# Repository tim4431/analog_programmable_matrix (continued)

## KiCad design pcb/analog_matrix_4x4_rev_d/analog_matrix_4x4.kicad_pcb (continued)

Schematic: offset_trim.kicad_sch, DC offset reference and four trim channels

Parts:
C169, C171, C173, C174, C176, C177, C179, C180, C182, C183, C187, C189: 100n; C_0603_1608Metric; Rating 25V X7R minimum; effective C after bias
C170, C172, C188, C190: 1u; C_0805_2012Metric; Rating 25V X7R minimum; effective C after bias
C175, C178, C181, C184: 100p C0G; C_0603_1608Metric; Rating 50V C0G
C185, C186: 10u; C_0805_2012Metric; Rating 25V X7R minimum; effective C after bias
U30: AD5544BRSZ; SSOP-28_5.3x10.2mm_P0.65mm
U100, U101, U102, U103: OPA197ID; SOIC-8_3.9x4.9mm_P1.27mm
U110: ADR4525BRZ; SOIC-8_3.9x4.9mm_P1.27mm

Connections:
+5A: C169.1, C170.1, C173.1, C176.1, C179.1, C182.1, C185.1, C187.1, C188.1, U30.7 (VDD), U100.7 (V+), U101.7 (V+), U102.7 (V+), U103.7 (V+), U110.2 (VIN); also elsewhere on the board
-5A: C171.1, C172.1, C174.1, C177.1, C180.1, C183.1, C186.1, U30.23 (VSS), U100.4 (V-), U101.4 (V-), U102.4 (V-), U103.4 (V-); also elsewhere on the board
GND: C169.2, C170.2, C171.2, C172.2, C173.2, C174.2, C176.2, C177.2, C179.2, C180.2, C182.2, C183.2, C185.2, C186.2, C187.2, C188.2, C189.2, C190.2, U30.1 (AGND), U30.5 (MSB), U30.14 (AGND), U30.15 (AGND), U30.22 (AGNDF), U30.24 (DGND), U30.28 (AGND), U100.3 (+), U101.3 (+), U102.3 (+), U103.3 (+), U110.4 (GND); also elsewhere on the board
LDAC_N: U30.21 (~LDAC); also elsewhere on the board
MOSI: U30.10 (SDI); also elsewhere on the board
unnamed: C175.1, U30.2 (IOUT), U100.2 (-)
unnamed: C178.1, U30.13 (IOUT), U101.2 (-)
unnamed: C181.1, U30.16 (IOUT), U102.2 (-)
unnamed: C184.1, U30.27 (IOUT), U103.2 (-)
RESET_N: U30.6 (~RS); also elsewhere on the board
SCK: U30.9 (CLK); also elsewhere on the board
TRIM_CS: U30.8 (~CS); also elsewhere on the board
VREF_2V5: C189.1, C190.1, U30.3 (VREF), U30.12 (VREF), U30.17 (VREF), U30.26 (VREF), U110.6 (2.5V); also elsewhere on the board
VTRIM0: C175.2, U30.4 (RFB), U100.6 (OUT); also elsewhere on the board
VTRIM1: C178.2, U30.11 (RFB), U101.6 (OUT); also elsewhere on the board
VTRIM2: C181.2, U30.18 (RFB), U102.6 (OUT); also elsewhere on the board
VTRIM3: C184.2, U30.25 (RFB), U103.6 (OUT); also elsewhere on the board

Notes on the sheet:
DC offset reference and four trim channels
U30 is a fifth AD5544. VTRIM=-2.5*D/65536 V. Midscale=32768. Loaded output trim is approximately +/-131 mV.
Offset trim for b0
Offset trim for b1
Offset trim for b2
Offset trim for b3

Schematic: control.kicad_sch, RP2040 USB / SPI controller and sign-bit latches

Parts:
C191, C192: 100n; C_0603_1608Metric; Rating 25V X7R minimum; effective C after bias
R133, R134, R135, R136, R137: 33R; R_0603_1608Metric; Rating 0.1%, <=25ppm/C; 0.1W minimum
R138, R139, R140, R141, R142, R143, R144, R145, R146: 10 k; R_0603_1608Metric; Rating 0.1%, <=25ppm/C; 0.1W minimum
U120: Pico; Pico_2x20_Socket_17.78mm
U121, U122: SN74HC595D; SOIC-16_3.9x9.9mm_P1.27mm

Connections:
3V3: C191.1, C192.1, R138.2, R139.2, R140.2, R141.2, R142.2, R143.2, U120.36 (3V3_OUT), U121.10 (~SRCLR), U121.16 (VCC), U122.10 (~SRCLR), U122.16 (VCC); also elsewhere on the board
/Control/MOSI_PRE: R134.1, U120.5 (GP3)
/Control/SCK_PRE: R133.1, U120.4 (GP2)
/Control/SIGN_CHAIN: U121.9 (QH'), U122.14 (SER)
/Control/SIGN_CLK: R136.2, U121.11 (SRCLK), U122.11 (SRCLK)
/Control/SIGN_CLK_PRE: R136.1, U120.15 (GP11)
/Control/SIGN_DATA: R135.2, U121.14 (SER)
/Control/SIGN_DATA_PRE: R135.1, U120.14 (GP10)
/Control/SIGN_LATCH: R137.2, U121.12 (RCLK), U122.12 (RCLK)
/Control/SIGN_LATCH_PRE: R137.1, U120.16 (GP12)
GND: C191.2, C192.2, R144.2, R145.2, R146.2, U120.3 (GND), U120.8 (GND), U120.13 (GND), U120.18 (GND), U120.23 (GND), U120.28 (GND), U120.33 (AGND), U120.38 (GND), U121.8 (GND), U121.13 (~OE), U122.8 (GND), U122.13 (~OE); also elsewhere on the board
LDAC_N: R143.1, U120.11 (GP8); also elsewhere on the board
MOSI: R134.2; also elsewhere on the board
OUTPUT_RUN: R146.1, U120.19 (GP14); also elsewhere on the board
RESET_N: R144.1, U120.12 (GP9); also elsewhere on the board
ROW0_CS: R138.1, U120.6 (GP4); also elsewhere on the board
ROW1_CS: R139.1, U120.7 (GP5); also elsewhere on the board
ROW2_CS: R140.1, U120.9 (GP6); also elsewhere on the board
ROW3_CS: R141.1, U120.10 (GP7); also elsewhere on the board
SCK: R133.2; also elsewhere on the board
SIGN0: U121.15 (QA); also elsewhere on the board
SIGN1: U121.1 (QB); also elsewhere on the board
SIGN2: U121.2 (QC); also elsewhere on the board
SIGN3: U121.3 (QD); also elsewhere on the board
SIGN4: U121.4 (QE); also elsewhere on the board
SIGN5: U121.5 (QF); also elsewhere on the board
SIGN6: U121.6 (QG); also elsewhere on the board
SIGN7: U121.7 (QH); also elsewhere on the board
SIGN8: U122.15 (QA); also elsewhere on the board
SIGN9: U122.1 (QB); also elsewhere on the board
SIGN10: U122.2 (QC); also elsewhere on the board
SIGN11: U122.3 (QD); also elsewhere on the board
SIGN12: U122.4 (QE); also elsewhere on the board
SIGN13: U122.5 (QF); also elsewhere on the board
SIGN14: U122.6 (QG); also elsewhere on the board
SIGN15: U122.7 (QH); also elsewhere on the board
SIGNAL_EN: R145.1, U120.17 (GP13); also elsewhere on the board
TRIM_CS: R142.1, U120.20 (GP15); also elsewhere on the board

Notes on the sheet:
RP2040 USB / SPI controller and sign-bit latches
Pico is USB-powered. Do not connect VBUS/VSYS to +5A. Apply analog power first. GP14=OUTPUT_RUN and GP13=SIGNAL_EN default low.
First register QA..QH = SIGN0..7. Second register QA..QH = SIGN8..15. Clock bit 15 first, latch after 16 clocks.
SPI mode 0, 1MHz, 24 clocks: last 18 bits = channel[1:0], code[15:0]. Five separate CS nets; shared LDAC. SDO pins intentionally unused. Firmware sequence: mute -> disable sign switches -> latch signs -> load 20 DAC words -> LDAC -> settle -> restore prior armed state. No automatic rail supervisor 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

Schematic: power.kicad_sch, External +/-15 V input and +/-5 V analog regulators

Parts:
C193, C197: 47u; C_Radial_D5.0mm_H11.0mm_P2.00mm; Rating 35V polarized
C194: 330n; C_0603_1608Metric; Rating 25V X7R minimum; effective C after bias
C195, C199: 10u; C_Radial_D5.0mm_H11.0mm_P2.00mm; Rating 16V polarized
C196, C200: 100n; C_0603_1608Metric; Rating 25V X7R minimum; effective C after bias
C198: 2.2u; CP_EIA-3216-18_Kemet-A; Rating 35V polarized
D1, D2: 1N4002; D_DO-41_SOD81_P10.16mm_Horizontal
J9: 3-pin terminal; TerminalBlock_Phoenix_MKDS-1,5-3-5.08_1x03_P5.08mm_Horizont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
U130: L7805CV; TO-220-3_Vertical
U131: L7905CV; TO-220-3_Vertical

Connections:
+5A: C195.1, C196.1, D1.2 (A), U130.3 (OUT); also elsewhere on the board
+15V: C193.1, C194.1, D1.1 (K), J9.1 (+15V), U130.1 (IN); also elsewhere on the board
-5A: C199.2, C200.1, D2.1 (K), U131.3 (OUT); also elsewhere on the board
-15V: C197.2, C198.2, D2.2 (A), J9.3 (-15V), U131.2 (IN); also elsewhere on the board
GND: C193.2, C194.2, C195.2, C196.2, C197.1, C198.1, C199.1, C200.2, J9.2 (GND), U130.2 (GND), U131.1 (GND); also elsewhere on the board

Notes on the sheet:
External +/-15 V input and +/-5 V analog regulators
External regulated +/-15 V, at least 1 A per rail. Regulator heatsinks <=15 C/W. Negative regulator tab is -15 V; positive regulator tab is GND.
Observe all polarized capacitor signs. Use the shown electrolytic/tantalum regulator capacitors; do not substitute ceramic-only outputs. Regulator dissipation is roughly 3 W per device; verify temperature under sustained DC output loads. +/-5A supplies the analog core.

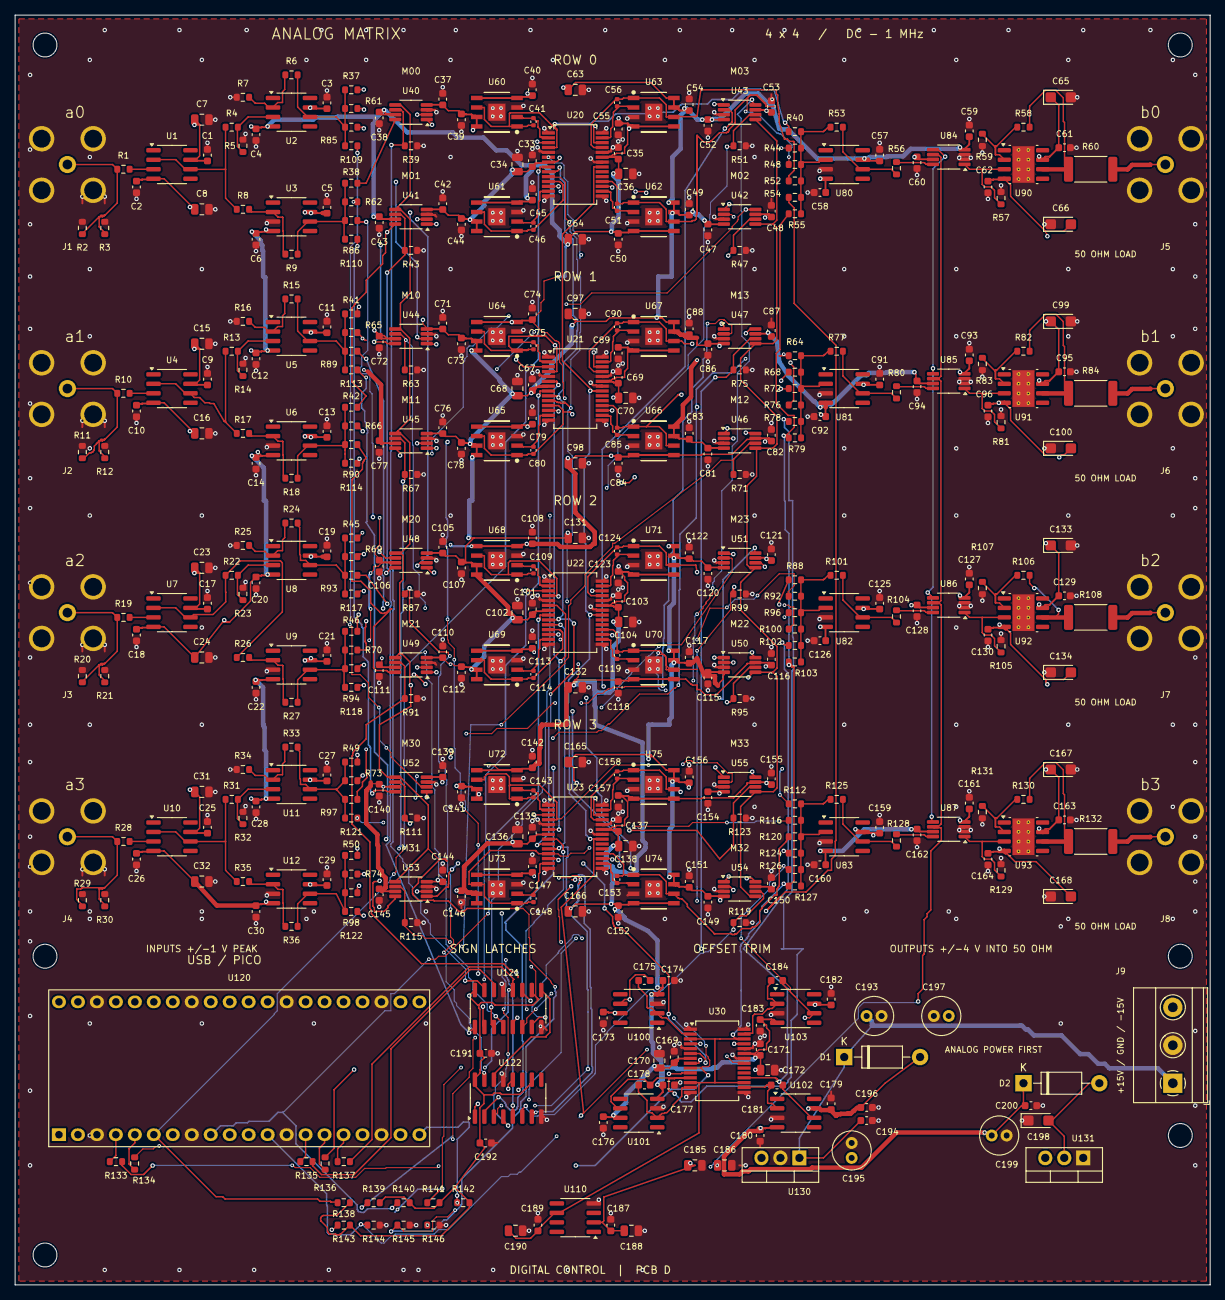
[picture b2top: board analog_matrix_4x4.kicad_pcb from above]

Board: 4 copper layers, 160.0 x 170.0 mm, 434 parts (0 on the bottom side), 191 nets.

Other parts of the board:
H1, H2, H3, H4, H5, H6: MountingHole_3.2mm_M3

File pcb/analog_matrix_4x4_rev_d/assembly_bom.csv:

References,Quantity,Value or IC MPN,Footprint,Rating,Fit
"J1, J2, J3, J4, J5, J6, J7, J8",8,BNC 031-5329-52RFX,AnalogMatrix:BNC_Amphenol_031-5329-52RFX_Vertical,,YES
"R1, R10, R19, R28, R133, R134, R135, R136, R137",9,33 ohm,AnalogMatrix:R_0603_1608Metric,"0.1%, <=25ppm/C; 0.1W minimum",YES
"R2, R11, R20, R29",4,1 M,AnalogMatrix:R_0603_1608Metric,"0.1%, <=25ppm/C; 0.1W minimum",YES
"R3, R12, R21, R30",4,49.9 ohm,AnalogMatrix:R_0603_1608Metric,"0.1%, <=25ppm/C; 0.1W minimum",DNP
"U1, U2, U3, U4, U5, U6, U7, U8, U9, U10, U11, U12, U80, U81, U82, U83",16,OPA810ID,AnalogMatrix:SOIC-8_3.9x4.9mm_P1.27mm,,YES
"C1, C2, C3, C4, C5, C6, C9, C10, C11, C12, C13, C14, C17, C18, C19, C20, C21, C22, C25, C26, C27, C28, C29, C30, C33, C35, C37, C38, C39, C40, C42, C43, C44, C45, C47, C48, C49, C50, C52, C53, C54, C55, C57, C58, C59, C60, C61, C62, C67, C69, C71, C72, C73, C74, C76, C77, C78, C79, C81, C82, C83, C84, C86, C87, C88, C89, C91, C92, C93, C94, C95, C96, C101, C103, C105, C106, C107, C108, C110, C111, C112, C113, C115, C116, C117, C118, C120, C121, C122, C123, C125, C126, C127, C128, C129, C130, C135, C137, C139, C140, C141, C142, C144, C145, C146, C147, C149, C150, C151, C152, C154, C155, C156, C157, C159, C160, C161, C162, C163, C164, C169, C171, C173, C174, C176, C177, C179, C180, C182, C183, C187, C189, C191, C192, C196, C200",136,100 nF,AnalogMatrix:C_0603_1608Metric,25V X7R minimum; effective C after bias,YES
"R4, R5, R13, R14, R22, R23, R31, R32",8,499 ohm,AnalogMatrix:R_0603_1608Metric,"0.1%, <=25ppm/C; 0.1W minimum",YES
"R6, R7, R8, R9, R15, R16, R17, R18, R24, R25, R26, R27, R33, R34, R35, R36, R40, R44, R48, R52, R64, R68, R72, R76, R88, R92, R96, R100, R112, R116, R120, R124",32,1.00 k,AnalogMatrix:R_0603_1608Metric,"0.1%, <=25ppm/C; 0.1W minimum",YES
"C7, C8, C15, C16, C23, C24, C31, C32, C63, C64, C97, C98, C131, C132, C165, C166, C185, C186",18,10 uF,AnalogMatrix:C_0805_2012Metric,25V X7R minimum; effective C after bias,YES
"U20, U21, U22, U23, U30",5,AD5544BRSZ,AnalogMatrix:SSOP-28_5.3x10.2mm_P0.65mm,,YES
"C34, C36, C68, C70, C102, C104, C136, C138, C170, C172, C188, C190",12,1 uF,AnalogMatrix:C_0805_2012Metric,25V X7R minimum; effective C after bias,YES
"R37, R38, R41, R42, R45, R46, R49, R50, R61, R62, R65, R66, R69, R70, R73, R74, R85, R86, R89, R90, R93, R94, R97, R98, R109, R110, R113, R114, R117, R118, R121, R122",32,150R 0.1%,AnalogMatrix:R_0603_1608Metric,"0.1%, <=25ppm/C; 0.1W minimum",YES
"U40, U41, U42, U43, U84, U44, U45, U46, U47, U85, U48, U49, U50, U51, U86, U52, U53, U54, U55, U87",20,TMUX6219DGKR,AnalogMatrix:VSSOP-8_3x3mm_P0.65mm,,YES
"R39, R43, R47, R51, R57, R63, R67, R71, R75, R81, R87, R91, R95, R99, R105, R111, R115, R119, R123, R129",20,100 k,AnalogMatrix:R_0603_1608Metric,"0.1%, <=25ppm/C; 0.1W minimum",YES
"U60, U61, U62, U63, U64, U65, U66, U67, U68, U69, U70, U71, U72, U73, U74, U75",16,ADA4899-1YRDZ,AnalogMatrix:ADA4899_RD8_EP2.29x2.29,,YES
"C41, C46, C51, C56, C75, C80, C85, C90, C109, C114, C119, C124, C143, C148, C153, C158",16,2.2 pF C0G ±0.1pF,AnalogMatrix:C_0402_1005Metric,50V C0G,YES
"R53, R77, R101, R125",4,523 ohm,AnalogMatrix:R_0603_1608Metric,"0.1%, <=25ppm/C; 0.1W minimum",YES
"R54, R78, R102, R126",4,10.0 k,AnalogMatrix:R_0603_1608Metric,"0.1%, <=25ppm/C; 0.1W minimum",YES
"R55, R79, R103, R127",4,20.0 k,AnalogMatrix:R_0603_1608Metric,"0.1%, <=25ppm/C; 0.1W minimum",YES
"R56, R80, R104, R128",4,49.9 ohm,AnalogMatrix:R_0603_1608Metric,"0.1%, <=25ppm/C; 0.1W minimum",YES
"U90, U91, U92, U93",4,THS3091DDAR,AnalogMatrix:SOIC-8-1EP_3.9x4.9mm_P1.27mm_EP2.95x4.9mm_Mask2.71x3.4mm_ThermalVias,,YES
"R58, R82, R106, R130",4,1.21 k,AnalogMatrix:R_0603_1608Metric,"0.1%, <=25ppm/C; 0.1W minimum",YES
"R59, R83, R107, R131",4,402 ohm,AnalogMatrix:R_0603_1608Metric,"0.1%, <=25ppm/C; 0.1W minimum",YES
"R60, R84, R108, R132",4,49.9 ohm,AnalogMatrix:R_2512_6332Metric,"0.1%, <=25ppm/C; >=1W",YES
"C65, C66, C99, C100, C133, C134, C167, C168",8,6.8 uF / 25 V,AnalogMatrix:CP_EIA-3216-18_Kemet-A,25V polarized,YES
"U100, U101, U102, U103",4,OPA197ID,AnalogMatrix:SOIC-8_3.9x4.9mm_P1.27mm,,YES
"C175, C178, C181, C184",4,100 pF C0G,AnalogMatrix:C_0603_1608Metric,50V C0G,YES
U110,1,ADR4525BRZ,AnalogMatrix:SOIC-8_3.9x4.9mm_P1.27mm,,YES
U120,1,Raspberry Pi Pico,AnalogMatrix:Pico_2x20_Socket_17.78mm,,YES
"U121, U122",2,SN74HC595D,AnalogMatrix:SOIC-16_3.9x9.9mm_P1.27mm,,YES
"R138, R139, R140, R141, R142, R143, R144, R145, R146",9,10 k,AnalogMatrix:R_0603_1608Metric,"0.1%, <=25ppm/C; 0.1W minimum",YES
J9,1,3-pin terminal,"AnalogMatrix:TerminalBlock_Phoenix_MKDS-1,5-3-5.08_1x03_P5.08mm_Horizontal",,YES
U130,1,L7805CV,AnalogMatrix:TO-220-3_Vertical,,YES
U131,1,L7905CV,AnalogMatrix:TO-220-3_Vertical,,YES
"D1, D2",2,1N4002,AnalogMatrix:D_DO-41_SOD81_P10.16mm_Horizontal,,YES
"C193, C197",2,47 uF / 35 V,AnalogMatrix:C_Radial_D5.0mm_H11.0mm_P2.00mm,35V polarized,YES
C194,1,330 nF,AnalogMatrix:C_0603_1608Metric,25V X7R minimum; effective C after bias,YES
"C195, C199",2,10 uF / 16 V,AnalogMatrix:C_Radial_D5.0mm_H11.0mm_P2.00mm,16V polarized,YES
C198,1,2.2 uF,AnalogMatrix:CP_EIA-3216-18_Kemet-A,35V polarized,YES

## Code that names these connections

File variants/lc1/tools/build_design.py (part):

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for ref in old_trim_refs:
    drop(ref)
for ref in ['R138','R139','R144','R145']:
    if ref in parts and any(n in ('LDAC_N','RESET_N','SIGNAL_EN','TRIM_CS') for n in parts[ref]['pins'].values()):
        drop(ref)
for ref, p in list(parts.items()):
    if ref.startswith('R') and any(n in ('LDAC_N','RESET_N','SIGNAL_EN','TRIM_CS') for n in p['pins'].values()):
        drop(ref)
for pin in ['11','12','17','20']:
    parts['U120']['pins'][pin]=None
parts['U120']['pins']['1']='TRIM_SDA'
parts['U120']['pins']['2']='TRIM_SCL'

box_symbol('MCP4728T-E_UN', [((-15.24,22.86,15.24,-22.86),[
    (1,'VDD',0,27.94,270,'power_in'),(2,'SCL',-20.32,12.7,0,'input'),
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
